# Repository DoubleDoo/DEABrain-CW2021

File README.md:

# DEABrain
Hardware and software system for monitoring and processing data of electrical activity of the brain

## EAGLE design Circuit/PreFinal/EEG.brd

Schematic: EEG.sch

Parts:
BOOT, BOOT1: BOOT; C0402
BUTTON1, BUTTON2: BUTTON
B_CAP_1, B_CAP_2: 0.1u; C0402
B_RESET: 1uf; C0402
B_RES_1, B_RES_4: 100om; R0402
B_RES_2, B_RES_5: 220om; R0402
B_RES_3, B_RES_6: 220k; R0402
C1: 10nf; C0402
C2: 4.7uf; C0402
ELECTROD: PIN-1
GBAT: PIN-1
GND: PIN-1
LED_1, LED_2, LED_3: LED; R0402
OSCILLATOR_RF: 32mhz; NX2520SA
OSC_C_1, OSC_C_2: 0; C0402
OSC_RF_C_3, OSC_RF_C_4: 0; C0402
R1: 60k; R0402
R2, R3: 50k; R0402
R4: 3.3k; R0402
R5, R9: 1k; R0402
R6: 0; R0402
R7: 470; R0402
R8: 10-50mO; R0402
R10: 200k; R0402
REF: PIN-1
RES_1_LED, RES_2_LED, RES_3_LED: 680om; R0402
RF_CAP_1, RF_CAP_2: 100pf; C0402
RG: 1Om; R0402
RSCL: 4.7K; R0402
RSDA: 4.7K; R0402
SMPS_C_1: 100nf; C0402
U$1: STM32WB55
U$2, U$6, U$14, U$29, U$30, U$32, U$54: 1uf; C0402
U$3: ANT
U$4: AD8422
U$5: TPS60403
U$7: LM358
U$8: MCP1703
U$9, U$11, U$12, U$13: 330nf; C0402
U$10: MLPF-WB55-01E3DEFAULT; MLPF-WB55-01E3
U$15, U$16: 60k; R0402
U$17, U$18: 9.5k; R0402
U$19, U$20, U$27, U$28: 0; R0402
U$21: M24M01
U$22: USBUSBT; USBT
U$23: SWDSWDD; SWD
U$24: STC3100
U$25: L6924D
U$26: BUTTON
U$31: RESISTORR0402; R0402
U$33: OSC_32KH; RESM2012X60N
U$47, U$48: 1k; R0402
U$49, U$50: LED; R0402
U$55: 220nf; C0402
USB_CAP_0, USB_CAP_1: 47p; C0402
USB_LED_1, USB_LED_2: LED; R0402
USB_LED_RES_1, USB_LED_RES_2: 5k; R0402
USB_RES_0, USB_RES_1: 22om; R0402
VBAT: PIN-1
VDDUSB_CAP_2: 0; C0402
VDD_CAP_1, VDD_CAP_5, VDD_CAP_7: 100nf; C0402
VDD_CAP_6: 4.7 uf; C0402
VDD_CAP_10: 1 uf; C0402

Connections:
GND: BOOT.1, B_RESET.2, B_RES_3.1, B_RES_6.1, C1.1, C2.1, GND.P$1, LED_1.2, LED_2.2, LED_3.2, OSCILLATOR_RF.1 (G1), OSC_C_1.2, OSC_C_2.2, OSC_RF_C_4.2, R1.2, R2.2, R3.2, R4.2, R7.2, R8.2, R10.1, RF_CAP_1.2, RF_CAP_2.2, SMPS_C_1.2, U$1.22 (VSSRF), U$1.32 (VSSSMPS), U$1.49 (VSSRF), U$2.1, U$4.6 (VREF), U$5.4 (GND), U$10.A2 (GND), U$10.B1 (GND), U$10.B2 (GND), U$10.C2 (GND), U$12.1, U$16.2, U$19.1, U$20.2, U$21.1 (E0), U$21.2 (E1), U$21.3 (E2), U$21.4 (GND), U$21.7 (WC), U$22.P$1 (GND), U$22.P$2 (GND), U$22.P$3 (GND), U$22.P$4 (GND), U$22.P$12 (GND), U$23.1 (GND), U$24.5 (GND), U$25.6 (GND), U$25.7 (SD), U$25.9 (VOPRG), U$25.17 (GND), U$26.2 (B2), U$30.1, U$32.1, U$54.1, U$55.2, USB_CAP_0.2, USB_CAP_1.2, USB_LED_1.2, USB_LED_2.2, VDDUSB_CAP_2.2, VDD_CAP_1.1, VDD_CAP_5.2, VDD_CAP_6.1, VDD_CAP_7.1, VDD_CAP_10.1
unnamed: U$1.21 (RF1), U$10.C1 (IN)
unnamed: BOOT.2, BOOT1.2, U$1.4 (BOOT0)
unnamed: U$1.39 (PA13), U$23.2 (SWDIO)
unnamed: OSCILLATOR_RF.2 (O1), OSC_RF_C_4.1, U$1.25 (OSC_IN_2)
unnamed: U$1.41 (PA14), U$23.3 (SWDCLK)
unnamed: RES_1_LED.1, U$1.30 (PE4)
unnamed: U$3.ANT_IN, U$10.A1 (OUT)
unnamed: RES_2_LED.1, U$1.29 (PB1)
unnamed: RES_3_LED.1, U$1.28 (PB0)
unnamed: LED_1.1, RES_1_LED.2
unnamed: LED_2.1, RES_2_LED.2
unnamed: LED_3.1, RES_3_LED.2
unnamed: U$1.37 (PA11), USB_CAP_0.1, USB_LED_RES_2.1, USB_RES_1.1
unnamed: U$1.38 (PA12), USB_CAP_1.1, USB_LED_RES_1.1, USB_RES_0.1
unnamed: R10.2, U$24.2 (ROSC)
unnamed: B_RES_5.2, U$1.9 (PA0)
unnamed: BUTTON1.2 (B2), B_CAP_2.2, B_RES_5.1, B_RES_6.2
unnamed: U$22.P$10 (D+), USB_RES_0.2
unnamed: U$22.P$13 (D-), USB_RES_1.2
unnamed: U$2.2, U$22.P$14 (VBUS), U$25.1 (VIN), U$25.2 (VINSNS), U$47.1, U$48.1
unnamed: R2.1, U$25.15 (IPRG)
unnamed: RSDA.2, U$1.47 (PB7), U$21.5 (SDA), U$24.3 (SDA)
unnamed: B_CAP_2.1, B_RES_4.2
unnamed: B_RES_2.2, U$1.10 (PA1)
unnamed: OSC_C_2.1, U$1.3 (OSC_OUT), U$33.1
unnamed: B_RESET.1, U$1.7 (NRST), U$26.1 (B1), U$31.1
unnamed: OSC_C_1.1, U$1.2 (OSC_IN), U$33.2
unnamed: USB_LED_2.1, USB_LED_RES_2.2
unnamed: OSCILLATOR_RF.3 (G2), OSC_RF_C_3.1
unnamed: C1.2, U$25.5 (TPRG)
unnamed: U$48.2, U$50.1
unnamed: U$47.2, U$49.1
unnamed: R3.1, U$25.16 (VPRE)
unnamed: U$25.3 (ST2), U$49.2
unnamed: U$25.4 (ST1), U$50.2
unnamed: R4.1, U$25.13 (IEND)
unnamed: R1.1, U$25.14 (IPRE)
unnamed: R9.2, U$24.8 (VIN), U$55.1
unnamed: R5.1, R7.1, U$25.8 (TH)
unnamed: R5.2, U$25.12 (VREF)
unnamed: RSCL.2, U$1.46 (PB6), U$21.6 (SCL), U$24.4 (SCL)
unnamed: R6.2, U$25.10 (VOSNS)
unnamed: GBAT.P$1, R8.1, U$24.6 (CG)
unnamed: USB_LED_1.1, USB_LED_RES_1.2
unnamed: RG.2, U$4.2 (RG1)
unnamed: RG.1, U$4.3 (RG2)
unnamed: REF.P$1, U$4.4 (+IN)
unnamed: ELECTROD.P$1, U$4.1 (-IN)
unnamed: U$4.7 (VOUT), U$9.1
unnamed: U$7.1 (O1), U$15.2, U$17.2, U$27.1
unnamed: U$7.3 (I1+), U$11.2, U$16.1
unnamed: U$9.2, U$11.1, U$15.1
unnamed: U$7.2 (I1-), U$19.2, U$27.2
unnamed: U$7.5 (I2+), U$12.2, U$18.1
unnamed: U$13.2, U$17.1, U$18.2
unnamed: U$1.13 (PA4), U$7.7 (O2), U$13.1, U$28.2
unnamed: U$7.6 (I2-), U$20.1, U$28.1
unnamed: BUTTON2.2 (B2), B_CAP_1.2, B_RES_2.1, B_RES_3.2
unnamed: U$6.1, U$8.1 (GND), U$14.1
unnamed: U$5.3 (CFLY-), U$29.1
unnamed: U$5.5 (CFLY+), U$29.2
unnamed: B_CAP_1.1, B_RES_1.2
unnamed: OSCILLATOR_RF.4 (O2), OSC_RF_C_3.2, U$1.24 (OSC_OUT_2)
V+: BOOT1.1, BUTTON1.1 (B1), BUTTON2.1 (B1), B_RES_1.1, B_RES_4.1, RF_CAP_1.1, RF_CAP_2.1, RSCL.1, RSDA.1, SMPS_C_1.1, U$1.1 (VBAT), U$1.8 (VDDA), U$1.20 (VDD), U$1.23 (VDDRF), U$1.31 (VFBSMPS), U$1.33 (VLXSMPS), U$1.34 (VDDSMPS), U$1.35 (VDD_2), U$1.40 (VDDUSB), U$1.48 (VDD_3), U$4.8 (+VS), U$5.2 (IN), U$6.2, U$7.8 (VCC+), U$8.2 (VOUT), U$21.8 (PWR), U$23.4 (PWR), U$31.2, U$32.2, VDDUSB_CAP_2.1, VDD_CAP_1.2, VDD_CAP_5.1, VDD_CAP_6.2, VDD_CAP_7.2, VDD_CAP_10.2
V-: U$4.5 (-VS), U$5.1 (OUT), U$7.4 (VCC-), U$30.2
VDD: C2.2, R6.1, R9.1, U$8.3 (VIN), U$14.2, U$24.7 (VCC), U$25.11 (VOUT), U$54.2, VBAT.P$1

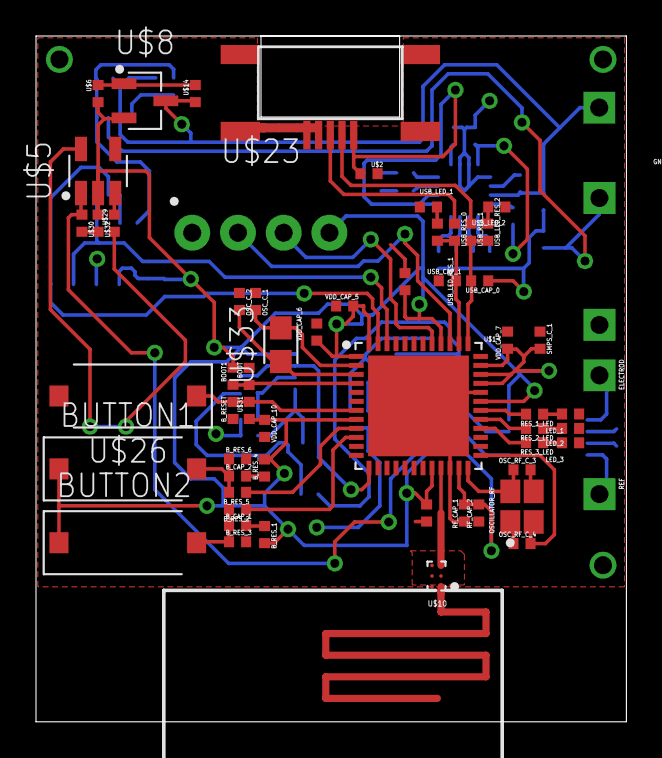
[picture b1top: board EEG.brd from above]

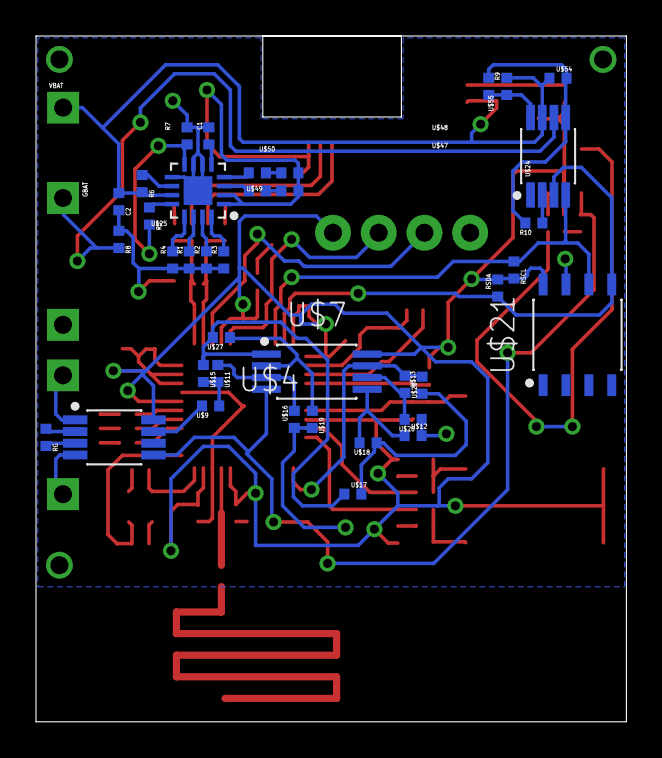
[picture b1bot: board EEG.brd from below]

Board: 2 copper layers, 32.8 x 38.1 mm, 100 parts (40 on the bottom side), 67 nets.

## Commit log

2020-11-08 Circuits and Resources commit
2021-02-02 reinit
2021-02-03 board development
2021-04-08 Add app prototype
2021-04-11 app development, add test EEG data
2021-04-12 rebuild react app
2021-04-12 ipc troubles solved
2021-04-12 bluetooth search finaly worked
2021-04-13 bluetoth development
2021-04-14 add test EEG data, add data simulation send, and chart prototypes
2021-04-18 options add, test py model add
2021-04-18 app development, settings menu fixed
2021-04-19 docs development
2021-04-20 eeg development
2021-04-20 docs development, app development
2021-04-20 development
2021-04-22 docs and net development
2021-04-23 code development
2021-04-23 restruct
2021-04-24 app development
2021-05-21 update data
2021-05-21 data upd
2021-05-21 add data
2021-05-21 gitignore change
2021-05-21 gitignore update
2021-05-22 document "Текст программы" development
2021-05-22 add case models, docs development
2021-05-22 doc development
2021-05-24 fixes
2021-05-25 fixes of eeg visualisation
2021-05-26 net isues
2021-05-26 base development finished
2021-05-26 "Руководство оператора" finished
2021-05-27 doc development finished
2021-05-27 docs development finished
2021-06-09 last update
